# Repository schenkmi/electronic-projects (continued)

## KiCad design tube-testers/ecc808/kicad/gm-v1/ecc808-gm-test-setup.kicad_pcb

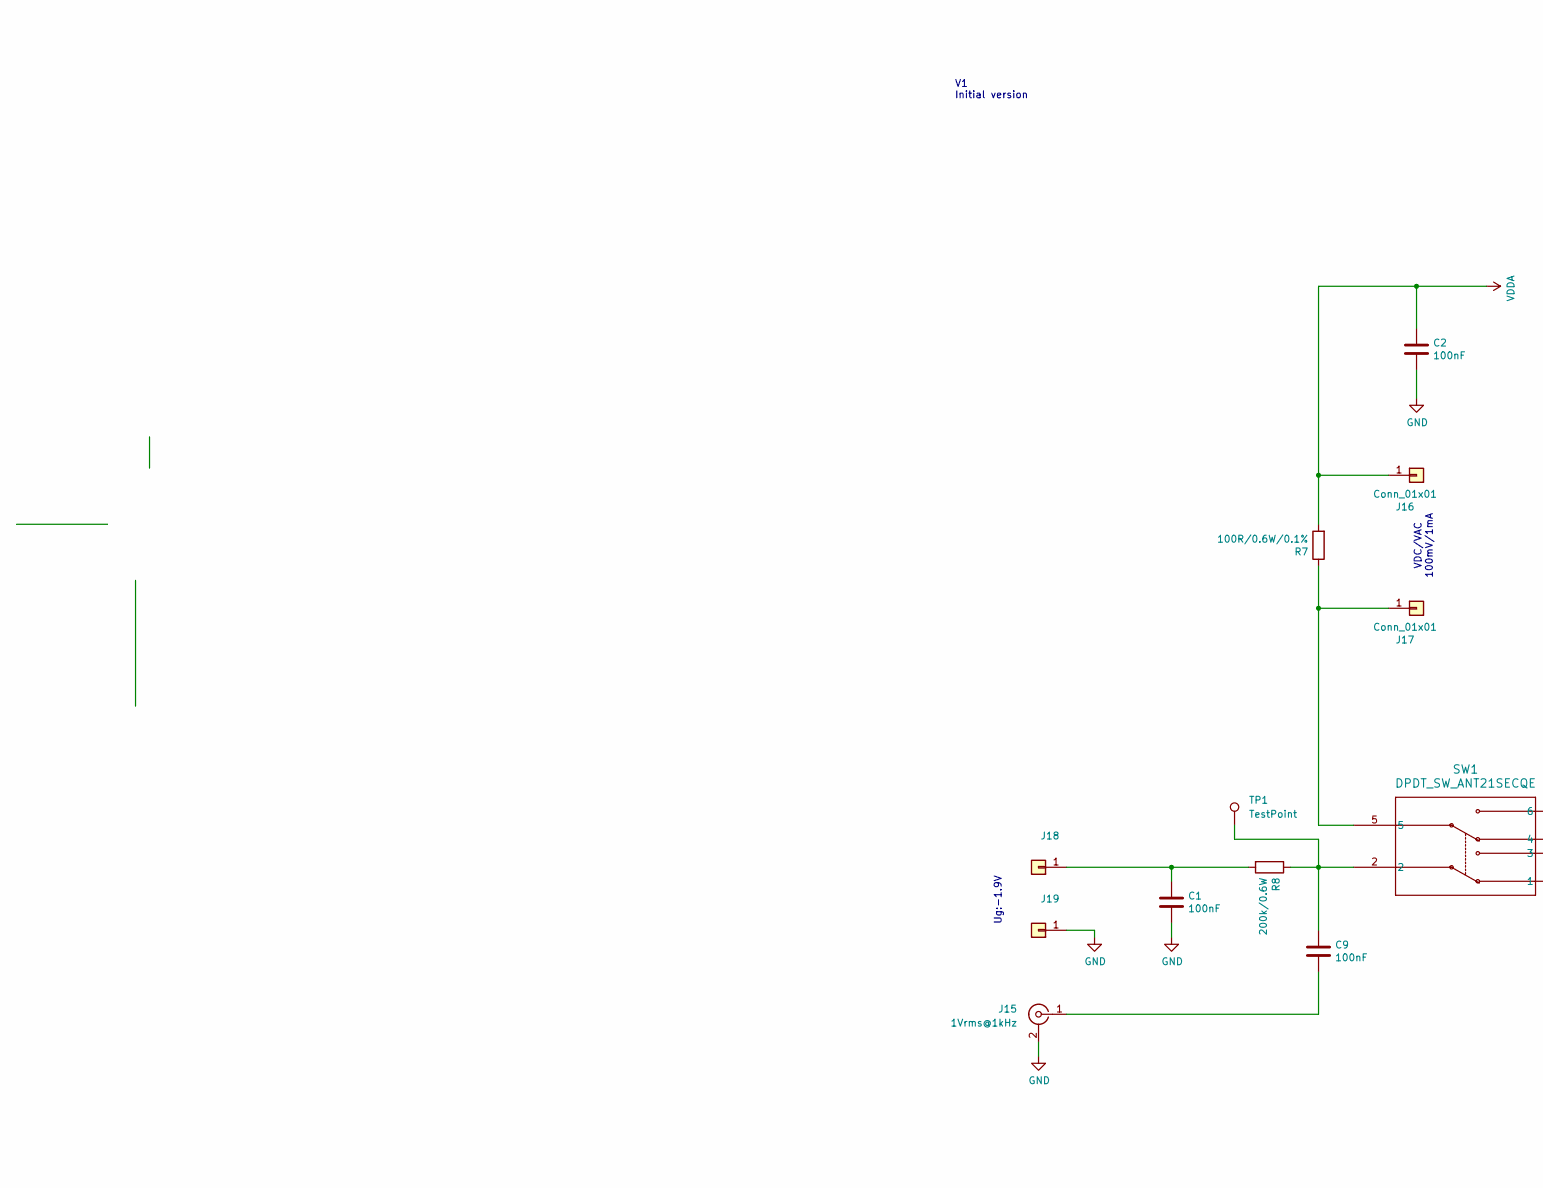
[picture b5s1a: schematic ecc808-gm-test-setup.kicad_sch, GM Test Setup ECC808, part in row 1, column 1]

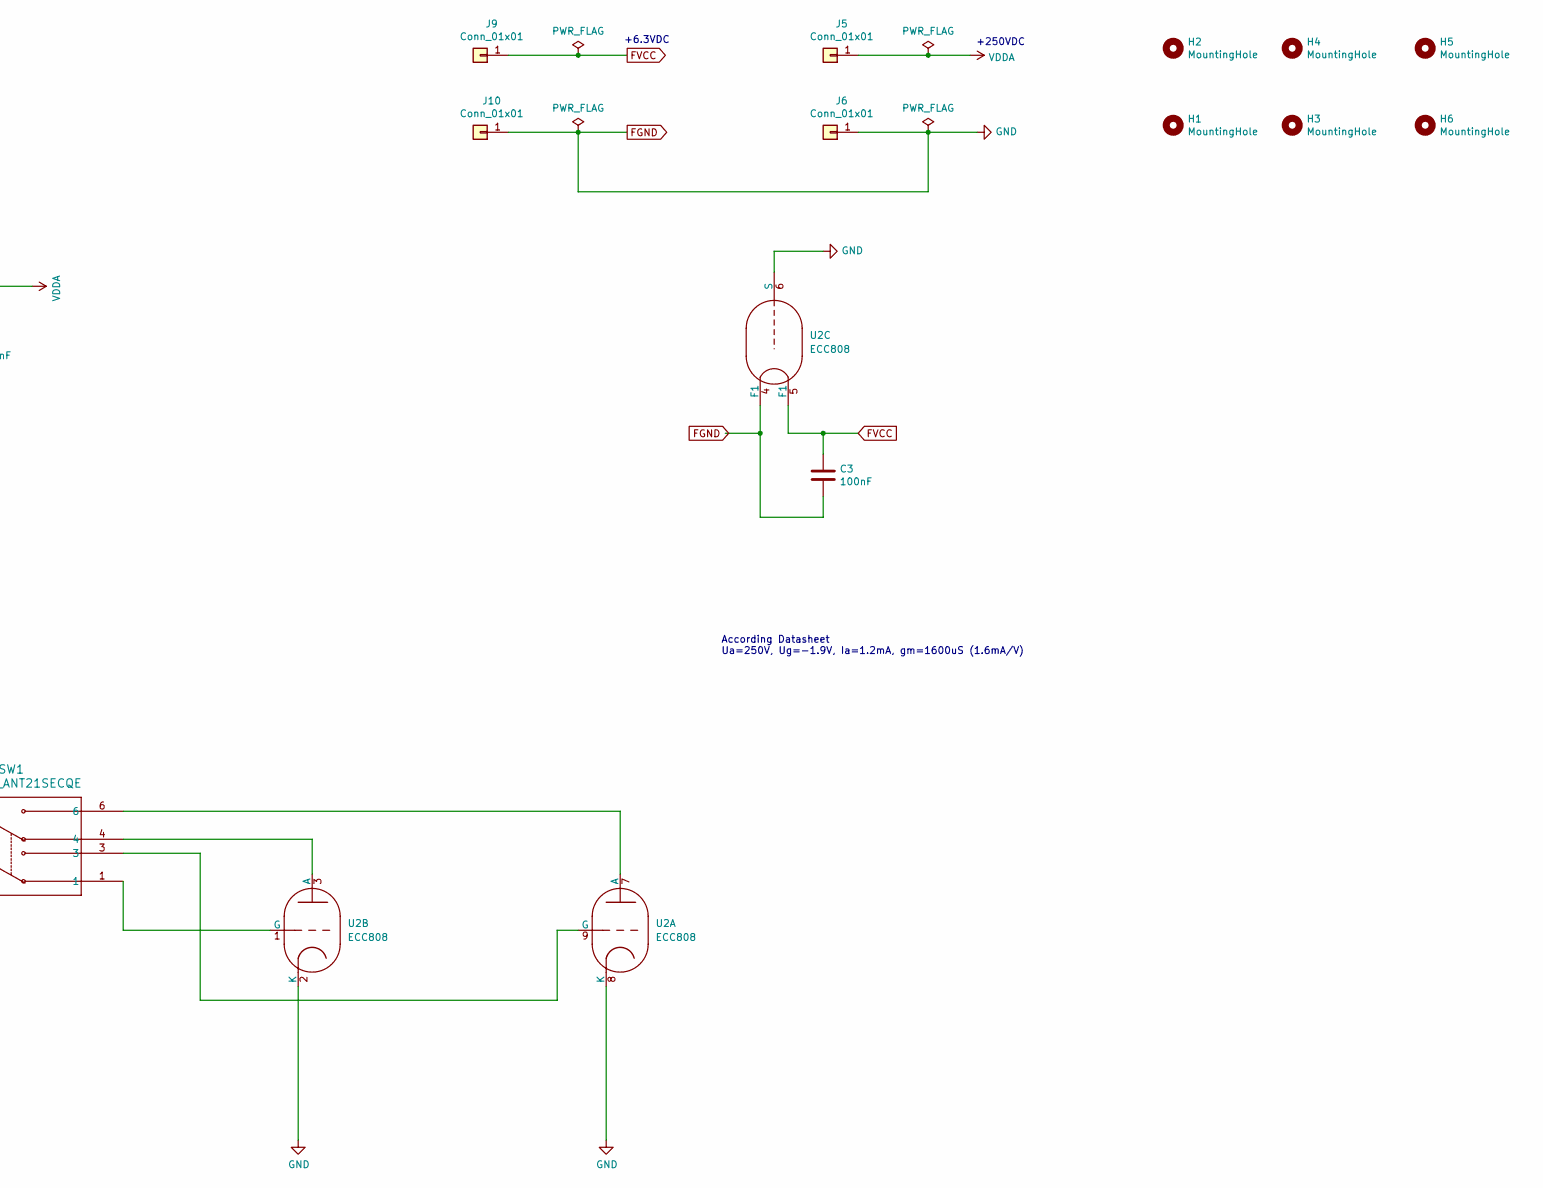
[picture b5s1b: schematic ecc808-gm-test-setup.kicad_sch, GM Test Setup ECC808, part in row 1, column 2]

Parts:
C1, C3, C9: 100nF; C_Rect_L7.2mm_W2.5mm_P5.00mm_FKS2_FKP2_MKS2_MKP2
C2: 100nF; C_Rect_L16.5mm_W5.0mm_P15.00mm_MKT
H1, H2, H3, H4, H5, H6: MountingHole; MountingHole_3.2mm_M3_Pad_Via
J5, J6, J9, J10: Conn_01x01; Pin_D1.3mm_L11.0mm
J15: 1Vrms@1kHz; RCA-Phono_CUI-Devices_RCJ-02X_Vertical
J16, J17: Conn_01x01; Pin_D1.0mm_L10.0mm
J18, J19: Pin_D1.0mm_L10.0mm
R7: 100R/0.6W/0.1%; R_Axial_DIN0207_L6.3mm_D2.5mm_P10.16mm_Horizontal
R8: 200k/0.6W; R_Axial_DIN0207_L6.3mm_D2.5mm_P10.16mm_Horizontal
SW1: DPDT_SW_ANT21SECQE; SW6_ANT21SECQE_CRS
TP1: TestPoint; TestPoint_Pad_D2.0mm
U2: ECC808; TubeNoval-ECC88

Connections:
FGND: C1.2, C2.2, C3.2, J6.1, J10.1, J15.2 (Ext), J19.1, U2.2 (K), U2.4 (F1), U2.6 (S), U2.8 (K)
FVCC: C3.1, J9.1, U2.5 (F1)
unnamed: C9.1, R8.1, SW1.2, TP1.1
unnamed: C9.2, J15.1 (In)
unnamed: J17.1, R7.1, SW1.5
unnamed: C1.1, J18.1, R8.2
unnamed: SW1.6, U2.7 (A)
unnamed: SW1.3, U2.9 (G)
unnamed: SW1.4, U2.3 (A)
unnamed: SW1.1, U2.1 (G)
VDDA: C2.1, J5.1, J16.1, R7.2

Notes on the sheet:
+6.3VDC
VDC/VAC 100mV/1mA
Ug:-1.9V
V1 Initial version
According Datasheet Ua=250V, Ug=-1.9V, Ia=1.2mA, gm=1600uS (1.6mA/V)
+250VDC

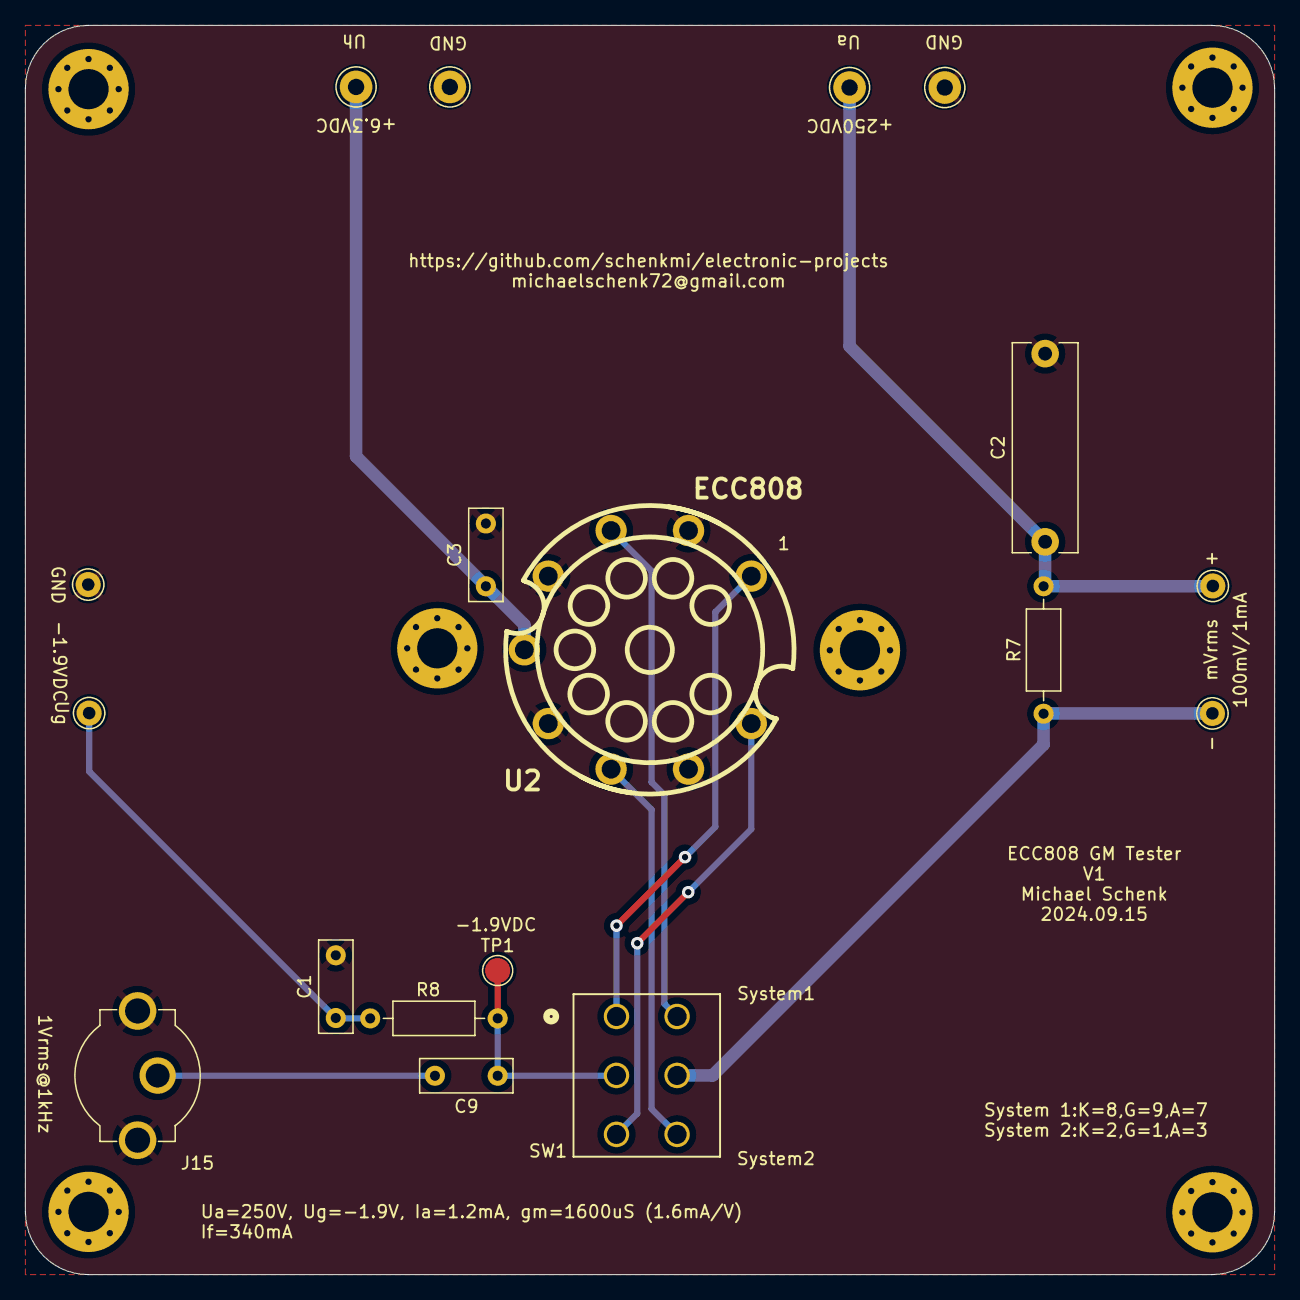
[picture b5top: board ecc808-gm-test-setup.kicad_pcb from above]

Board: 2 copper layers, 99.6 x 99.6 mm, 24 parts (0 on the bottom side), 11 nets.
